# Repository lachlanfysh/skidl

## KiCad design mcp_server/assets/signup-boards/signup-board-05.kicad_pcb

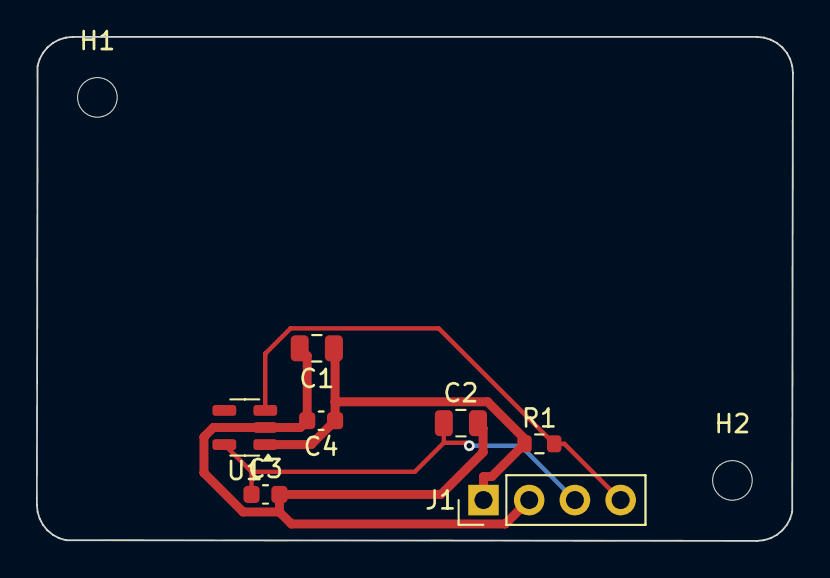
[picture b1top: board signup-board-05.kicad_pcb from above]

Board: 2 copper layers, 42.0 x 28.0 mm, 9 parts (0 on the bottom side), 4 nets.

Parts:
C1, C2: 10uF; C_0805_2012Metric
C3, C4: 100nF; C_0603_1608Metric
H1, H2: MountingHole; MountingHole_2.2mm_M2
J1: Conn_01x04; PinHeader_1x04_P2.54mm_Vertical
R1: 100K; R_0603_1608Metric
U1: AP2112K-3.3; SOT-23-5

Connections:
3V3: C2.1, C3.1, J1.3, U1.5
EN: J1.4, R1.2, U1.3
GND: C1.2, C2.2, C3.2, C4.2, J1.2, U1.2
VIN: C1.1, C4.1, J1.1, R1.1, U1.1

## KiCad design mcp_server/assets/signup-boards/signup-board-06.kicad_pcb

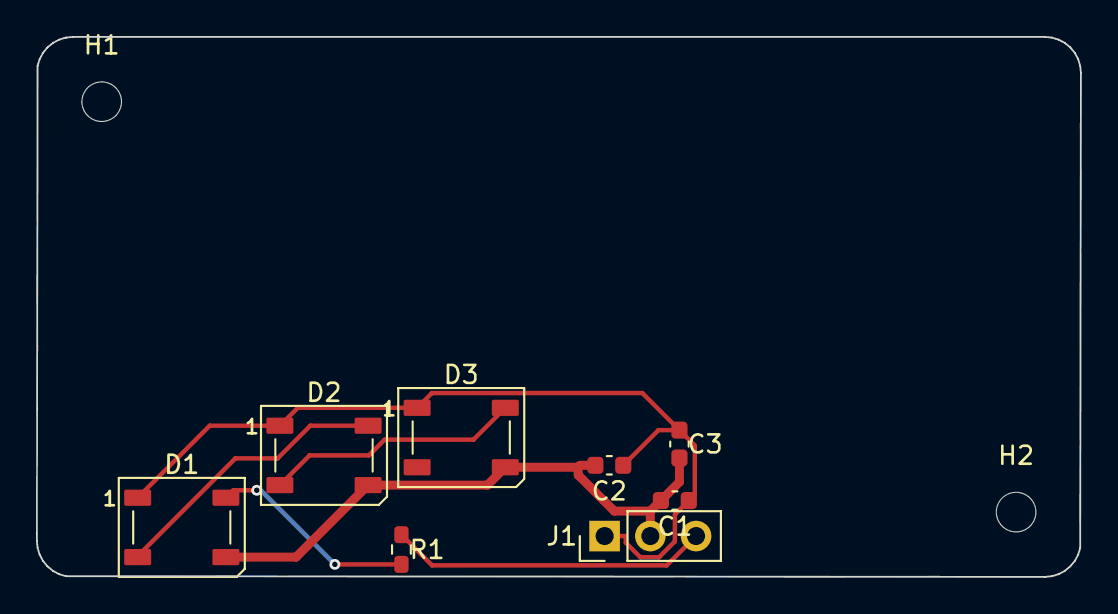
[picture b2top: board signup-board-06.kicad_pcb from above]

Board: 2 copper layers, 58.0 x 30.0 mm, 10 parts (0 on the bottom side), 6 nets.

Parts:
C1, C2, C3: 100nF; C_0603_1608Metric
D1, D2, D3: WS2812B; LED_WS2812B_PLCC4_5.0x5.0mm_P3.2mm
H1, H2: MountingHole; MountingHole_2.2mm_M2
J1: Conn_01x03; PinHeader_1x03_P2.54mm_Vertical
R1: 330; R_0603_1608Metric

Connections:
5V: C1.1, C2.1, C3.1, D1.1, D2.1, D3.1, J1.1
D1_OUT: D1.2, D2.4
D2_OUT: D2.2, D3.4
DIN: J1.3, R1.1
GND: C1.2, C2.2, C3.2, D1.3, D2.3, D3.3, J1.2
unnamed: D1.4, R1.2

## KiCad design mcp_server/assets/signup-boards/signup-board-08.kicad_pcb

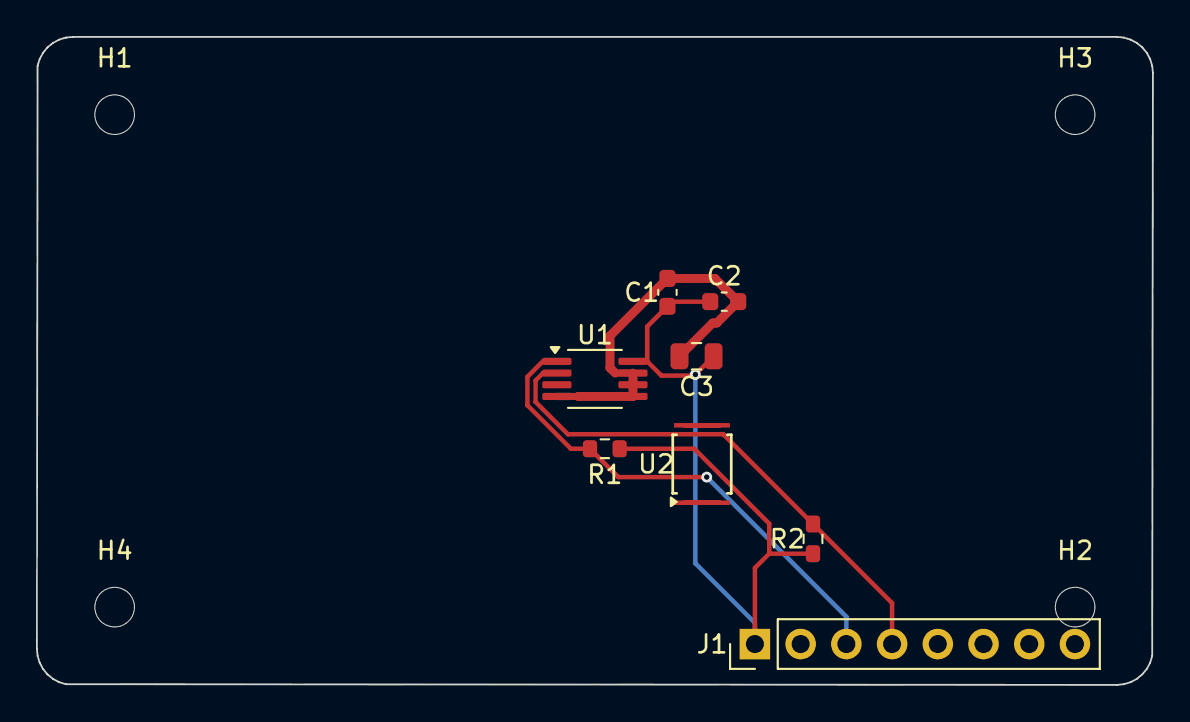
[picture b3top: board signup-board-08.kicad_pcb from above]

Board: 2 copper layers, 62.0 x 36.0 mm, 12 parts (0 on the bottom side), 8 nets.

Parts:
C1, C2: 100nF; C_0603_1608Metric
C3: 10uF; C_0805_2012Metric
H1, H2, H3, H4: MountingHole; MountingHole_2.2mm_M2
J1: Conn_01x08; PinHeader_1x08_P2.54mm_Vertical
R1, R2: 10K; R_0603_1608Metric
U1: MCP9808_MSOP; MSOP-8_3x3mm_P0.65mm
U2: ADS1115IDGS; TSSOP-10_3x3mm_P0.5mm

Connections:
3V3: C1.1, C2.1, C3.1, J1.1, R1.1, R2.1, U1.8, U2.8
GND: C1.2, C2.2, C3.2, J1.2, U1.4, U1.5, U1.6, U1.7, U2.1, U2.3
unnamed: J1.5, U2.4
unnamed: J1.6, U2.5
unnamed: J1.7, U2.6
unnamed: J1.8, U2.7
SCL: J1.4, R2.2, U1.2, U2.10
SDA: J1.3, R1.2, U1.1, U2.9

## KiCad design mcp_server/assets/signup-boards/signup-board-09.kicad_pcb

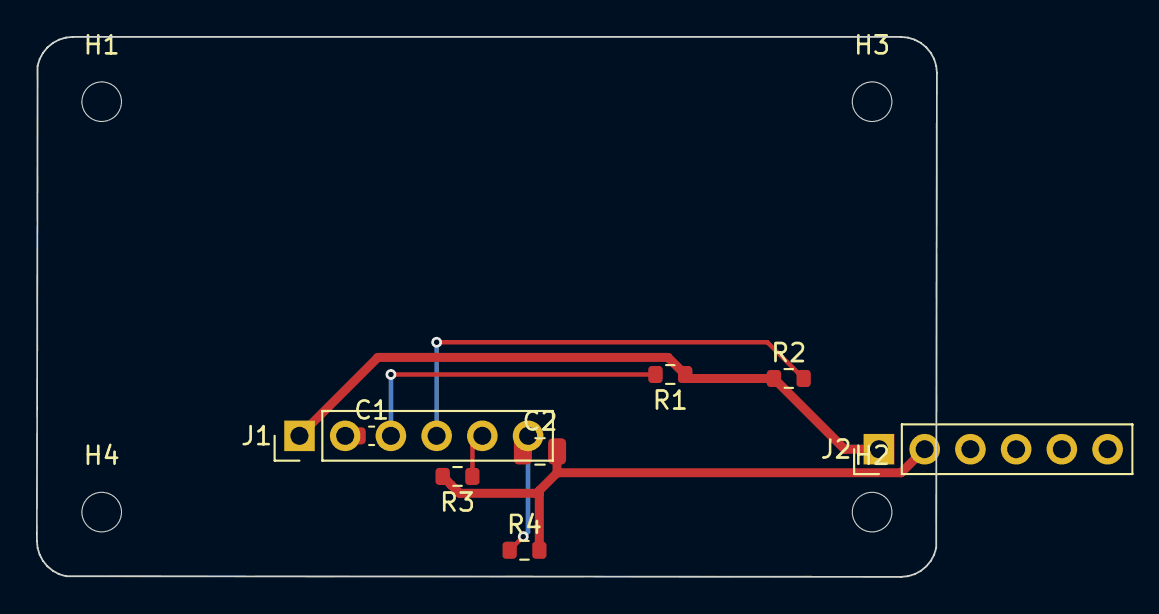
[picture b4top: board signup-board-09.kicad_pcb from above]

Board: 2 copper layers, 50.0 x 30.0 mm, 12 parts (0 on the bottom side), 6 nets.

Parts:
C1: 100nF; C_0603_1608Metric
C2: 10uF; C_0805_2012Metric
H1, H2, H3, H4: MountingHole; MountingHole_2.2mm_M2
J1, J2: Conn_01x06; PinHeader_1x06_P2.54mm_Vertical
R1: 1K; R_0603_1608Metric
R2: 2K2; R_0603_1608Metric
R3: 4K7; R_0603_1608Metric
R4: 10K; R_0603_1608Metric

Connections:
GND: C1.2, C2.2, J1.2, J2.2, R3.2, R4.2
SIG1: J1.3, J2.3, R1.2
SIG2: J1.4, J2.4, R2.2
SIG3: J1.5, J2.5, R3.1
SIG4: J1.6, J2.6, R4.1
VCC: C1.1, C2.1, J1.1, J2.1, R1.1, R2.1

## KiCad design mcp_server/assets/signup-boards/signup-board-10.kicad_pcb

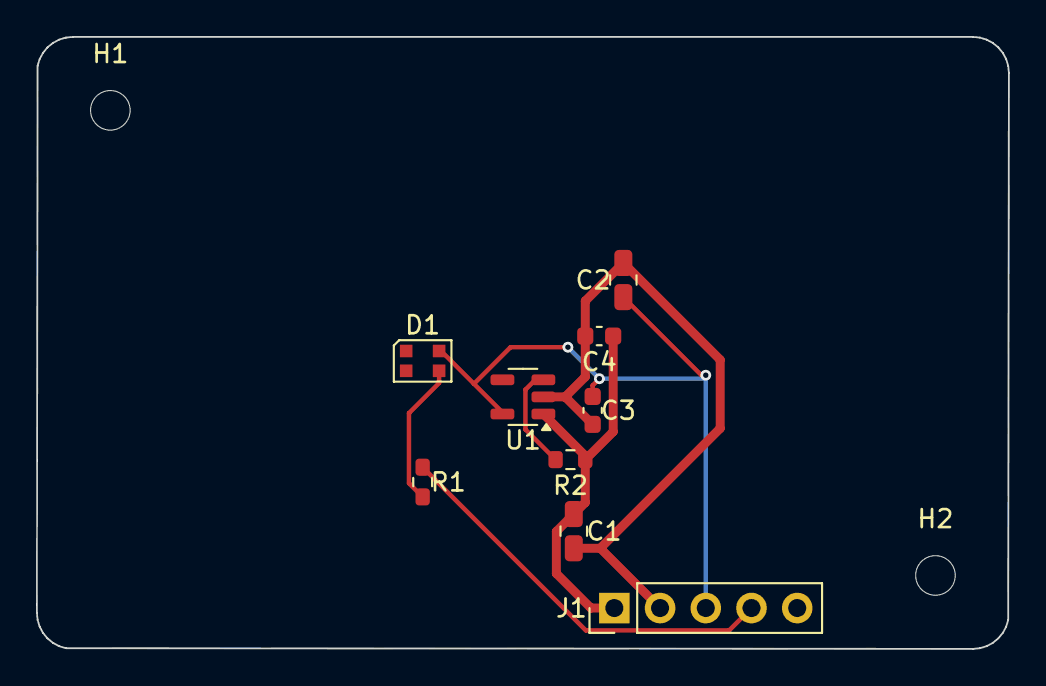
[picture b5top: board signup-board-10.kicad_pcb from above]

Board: 2 copper layers, 54.0 x 34.0 mm, 11 parts (0 on the bottom side), 7 nets.

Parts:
C1, C2: 10uF; C_0805_2012Metric
C3, C4: 100nF; C_0603_1608Metric
D1: WS2812B-2020; LED_WS2812B-2020_PLCC4_2.0x2.0mm
H1, H2: MountingHole; MountingHole_2.2mm_M2
J1: Conn_01x05; PinHeader_1x05_P2.54mm_Vertical
R1: 330; R_0603_1608Metric
R2: 100K; R_0603_1608Metric
U1: AP2112K-3.3; SOT-23-5

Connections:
3V3: C2.1, C3.1, D1.4, J1.3, U1.5
DATA: J1.4, R1.1
GND: C1.2, C2.2, C3.2, C4.2, D1.2, J1.2, U1.2
unnamed: R2.2, U1.3
unnamed: D1.3, R1.2
unnamed: D1.1, J1.5
VIN: C1.1, C4.1, J1.1, R2.1, U1.1
